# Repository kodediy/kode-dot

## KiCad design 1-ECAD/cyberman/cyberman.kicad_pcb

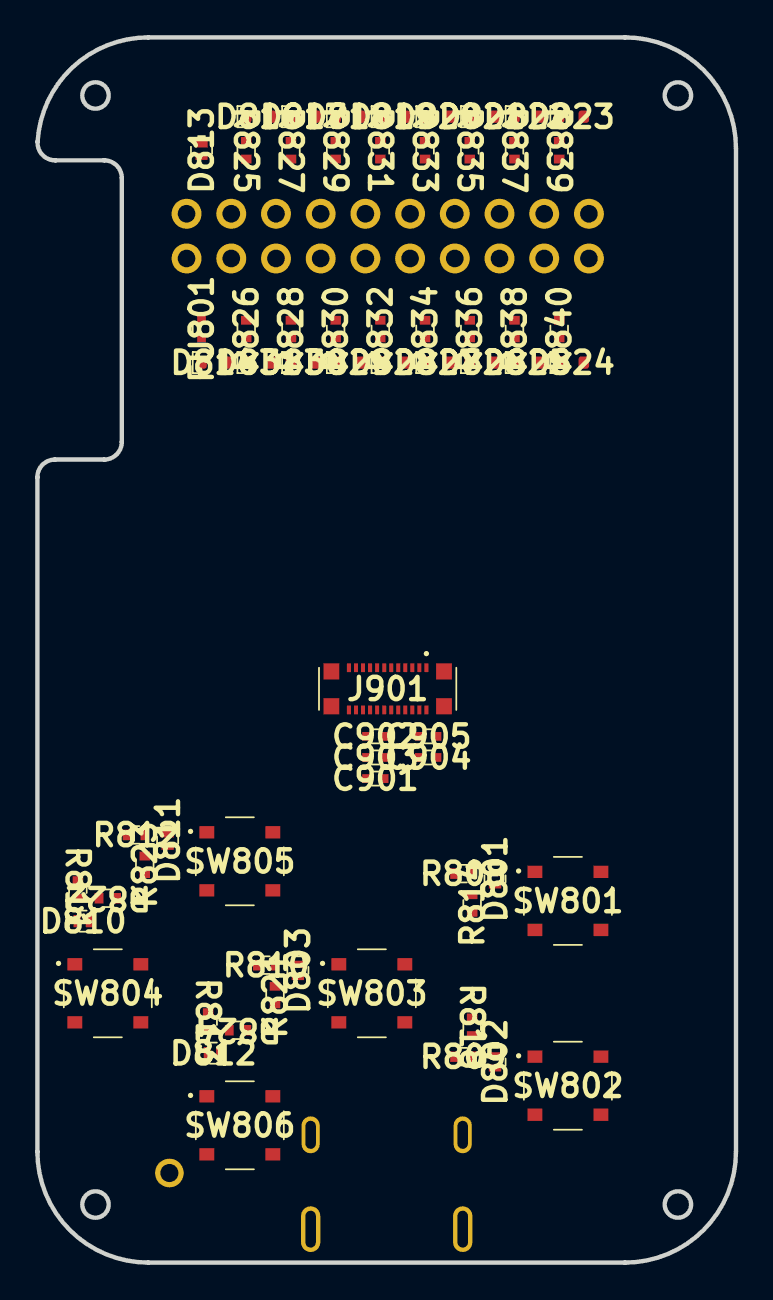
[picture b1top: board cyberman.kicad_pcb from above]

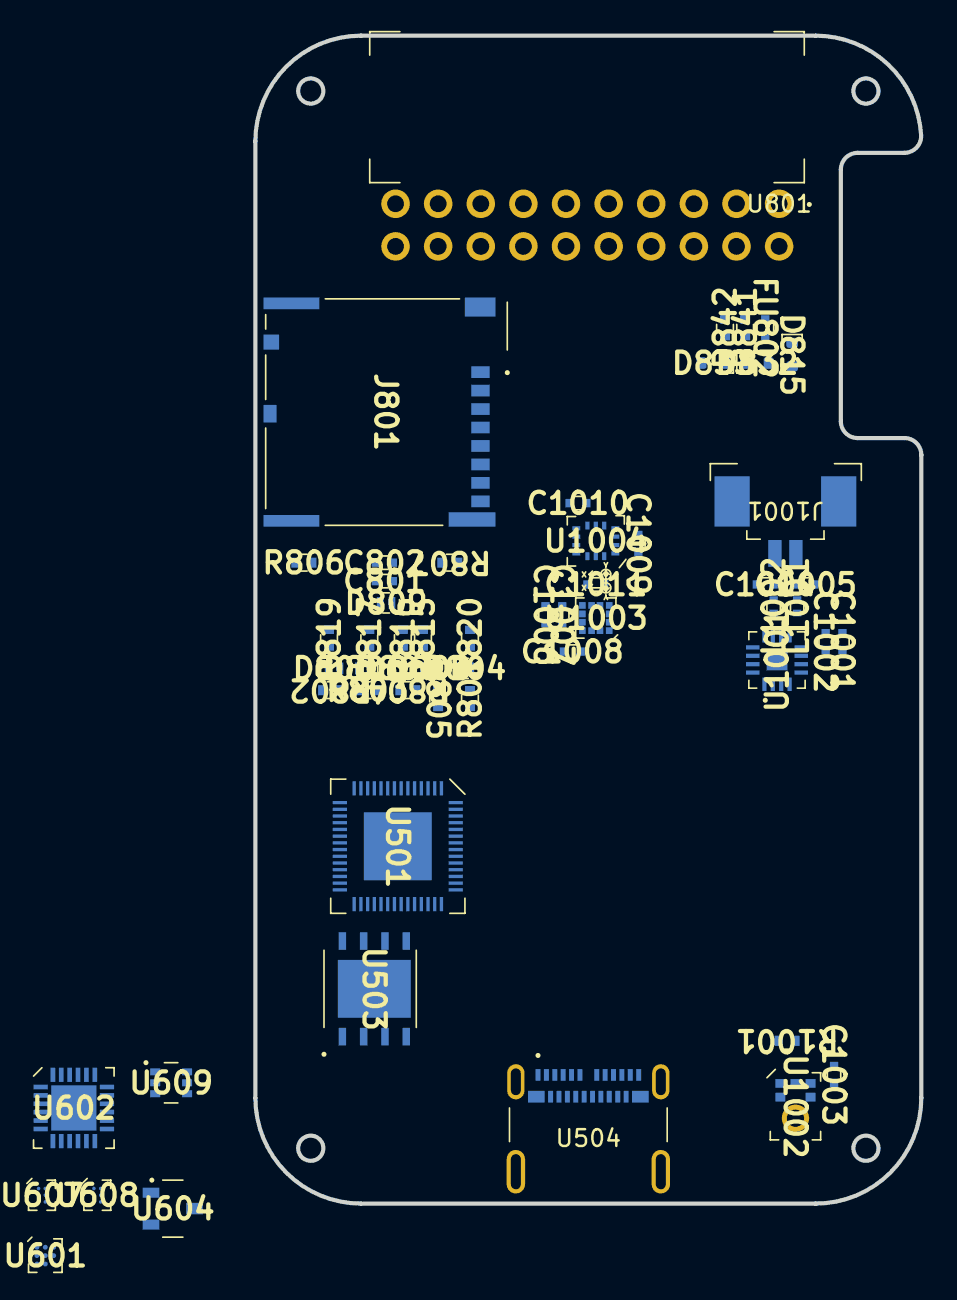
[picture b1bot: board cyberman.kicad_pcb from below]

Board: 4 copper layers, 39.7 x 69.6 mm, 121 parts (56 on the bottom side), 85 nets, no tracks yet.

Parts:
C801, C802, C901, C904, C1001, C1006: CC0402MRX5R6BB106; C_0402
C902, C903, C905, C1002, C1003, C1007, C1008, C1009, C1010: CC0402KRX7R8BB104; C_0402
C1004, C1005: CC0402KRX7R8BB221; C_0402
C1011: CC0402KRX5R8BB224; C_0402
D801, D802, D803, D804, D805, D806, D807, D808, D809, D810, D811, D812, D813: LESD8D3.3CAT5G
D814, D815, D816, D817, D818, D819, D820, D821, D822, D823, D824, D825, D826, D827, D828, D829, D830, D831, D832, D833: LESD5D5.0CT1G
FU801, FU802: ERBRD2R00X; ERBRD0R63X
J801: 5033981892
J901: YXT-BB10-24S-02
J1001: 532610271
L1001, L1002: BLM15PX331SZ1D
R801, R802, R803, R804, R805, R806, R807: RC0402FR-0747KL; R_0402
R808, R809, R810, R811, R812, R813: RC0402FR-0710KL; R_0402
R814, R818, R821, R822, R823, R824: RC0402FR-07330RL; R_0402
R815, R820: RC0402FR-07150RL; R_0402
R816, R817, R819, R825, R826, R827, R828, R829, R830, R831, R832, R833, R834, R835, R836, R837, R838, R839, R840, R841, R842: RC0402FR-0751RL; R_0402
R1001: RC0402FR-07100KL; R_0402
SW801, SW802, SW803, SW804, SW805, SW806: SKRMAAE010
U501: ESP32-S3R16V
U503: W25Q128JWPIQ
U504: 1054500101
U601: BQ27220YZFR
U602: BQ25896RTWR
U604: RS3221-3.3YF3
U607, U608: LM3281YFQR
U609: MMDT2907A-7-F
U801: PM254-2-10-W-8.5
U1001: MAX98357A; MAX98357AETE+T
U1002: ICS-43434
U1003: LIS2MDLTR
U1004: LSM6DSOTR

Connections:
+3V3: C1001.1, C1002.1, C1003.1, C1006.1, C1007.1, C1008.1, C1009.1, C1010.1, R808.1, R809.1, R810.1, R811.1, R812.1, R813.1, U608.A1 (FB), U1001.7 (VDD), U1001.8 (VDD), U1002.5 (VDD), U1003.3 (CS), U1003.9 (VDD), U1003.10 (VDDIO), U1004.1 (SDO/SA0), U1004.5 (VDDIO), U1004.8 (VDD), U1004.12 (CS)
+BATT: U601.C1 (SRP), U601.C3 (BAT)
/Project Architecture/Display/DSP.RST: J901.9 (RST), J901.21 (TP-RST)
/Project Architecture/MCU - IOs/BUTTON.BACK: R818.1, U501.37 (SPICLK_P)
/Project Architecture/MCU - IOs/BUTTON.SELECT: R814.1, U501.36 (SPICLK_N)
/Project Architecture/MCU - IOs/SD.CD: D804.1, R801.2, R820.1
/Project Architecture/MCU - IOs/SD.CLK: D806.1, R803.2, R817.1, U501.23 (GPIO17)
/Project Architecture/MCU - IOs/SD.CS: D808.1, R805.2, R815.1, U501.22 (XTAL_32K_N)
/Project Architecture/MCU - IOs/SD.MISO: D805.1, R802.2, R819.1, U501.27 (GPIO21)
/Project Architecture/MCU - IOs/SD.MOSI: D807.1, R804.2, R816.1, U501.24 (GPIO18)
/Project Architecture/MCU - IOs/SPICLK: U501.33 (SPICLK), U503.6 (CLK)
/Project Architecture/MCU - IOs/SPICS0: U501.32 (SPICS0), U503.1 (~CS)
/Project Architecture/MCU - IOs/SPID: U501.35 (SPID), U503.5 (DI(IO0))
/Project Architecture/MCU - IOs/SPIHD: U501.30 (SPIHD), U503.7 (IO3)
/Project Architecture/MCU - IOs/SPIQ: U501.34 (SPIQ), U503.2 (DO(IO1))
/Project Architecture/MCU - IOs/SPIWP: U501.31 (SPIWP), U503.3 (IO2)
/Project Architecture/Peripherals/1: D816.1, R825.1
/Project Architecture/Peripherals/2: D817.1, R827.1
/Project Architecture/Peripherals/3: D818.1, R829.1
/Project Architecture/Peripherals/4: D819.1, R831.1
/Project Architecture/Peripherals/5: D820.1, R833.1
/Project Architecture/Peripherals/6: D821.1, R835.1
/Project Architecture/Peripherals/7: D822.1, R837.1
/Project Architecture/Peripherals/8: D823.1, R839.1
/Project Architecture/Peripherals/9: D831.1, R826.1
/Project Architecture/Peripherals/10: D830.1, R828.1
/Project Architecture/Peripherals/11: D829.1, R830.1
/Project Architecture/Peripherals/12: D828.1, R832.1
/Project Architecture/Peripherals/13: D827.1, R834.1
/Project Architecture/Peripherals/14: D826.1, R836.1
/Project Architecture/Peripherals/15: D825.1, R838.1
/Project Architecture/Peripherals/16: D824.1, R840.1
/Project Architecture/Peripherals/BOARD_I2C.SCL: D832.1, R841.1
/Project Architecture/Peripherals/BOARD_I2C.SDA: D833.1, R842.1
/Project Architecture/Sensors and Audio/I2C_BOARD.SCL: U1003.1 (SCL/SPC), U1004.13 (SCL)
/Project Architecture/Sensors and Audio/I2C_BOARD.SDA: U1003.4 (SDA/SDI/SDO), U1004.14 (SDA)
/Project Architecture/Sensors and Audio/I2S.SCK: U1001.16 (BCLK), U1002.4 (SCK)
/Project Architecture/Sensors and Audio/I2S.SD: R1001.1, U1001.1 (DIN), U1002.6 (SD)
/Project Architecture/Sensors and Audio/I2S.WS: U1001.14 (LRCLK), U1002.1 (WS)
EXT_3V3: C801.1, C802.1, C901.1, C902.1, C903.1, C904.1, C905.1, D809.1, D813.2, J801.4 (VDD), J901.15 (VCC), J901.16 (VCI_EN), J901.17 (VBAT), J901.23 (TP-VDD), R801.1, R802.1, R803.1, R804.1, R805.1, R806.1, R807.1, U607.A1 (FB), U801.1
GND: C801.2, C802.2, C901.2, C902.2, C903.2, C904.2, C905.2, C1001.2, C1002.2, C1003.2, C1004.2, C1005.2, C1006.2, C1007.2, C1008.2, C1009.2, C1010.2, C1011.2, D801.2, D802.2, D803.2, D804.2, D805.2, D806.2, D807.2, D808.2, D809.2, D810.2, D811.2, D812.2, D813.1, D814.2, D815.2, D816.2, D817.2, D818.2, D819.2, D820.2, D821.2, D822.2, D823.2, D824.2, D825.2, D826.2, D827.2, D828.2, D829.2, D830.2, D831.2, D832.2, D833.2, J801.6 (VSS), J801.9 (VSS), J901.13 (GND), J901.18 (GND), J901.24 (GND), J901.P1 (SHELL), J901.P2 (SHELL), J901.P3 (SHELL), J901.P4 (SHELL), R1001.2, SW801.2, SW802.2, SW803.2, SW804.2, SW805.2, SW806.2, U503.4 (GND), U504.A1 (GND), U504.A12 (GND), U504.B1 (GND), U504.B12 (GND), U601.B2 (VSS), U602.9 (~CE), U602.17 (PGND), U602.18 (PGND), U604.1 (GND), U801.19, U801.20, U1001.3 (GND), U1001.11 (GND), U1001.15 (GND), U1001.17 (EP), U1002.2 (LR), U1002.3 (GND), U1003.6 (GND), U1003.8 (GND), U1004.2 (SDx), U1004.3 (SCx), U1004.6 (GND), U1004.7 (GND)
GNDPWR_EXT: U607.C2 (GND), U608.C2 (GND)
unnamed: U504.A6 (D+), U504.B6 (D+)
unnamed: U504.A7 (D-), U504.B7 (D-)
unnamed: U602.19 (SW), U602.20 (SW)
unnamed: D801.1, R808.2, R814.2, SW801.1
unnamed: D802.1, R809.2, R818.2, SW802.1
unnamed: D803.1, R810.2, R821.2, SW803.1
unnamed: D810.1, R811.2, R822.2, SW804.1
unnamed: D811.1, R812.2, R823.2, SW805.1
unnamed: D812.1, R813.2, R824.2, SW806.1
unnamed: FU801.2, U801.2
unnamed: J801.2 (CD/DAT3), R815.2
unnamed: J801.5 (CLK), R817.2
unnamed: J801.3 (CMD), R816.2
unnamed: J801.7 (DAT0), R819.2
unnamed: J801.8 (DAT1), R806.2
unnamed: J801.1 (DAT2), R807.2
unnamed: J801.10 (SW_DTCT), R820.2
unnamed: C1005.1, J1001.1, L1001.2
unnamed: C1004.1, J1001.2, L1002.2
unnamed: U609.2, U609.3, U609.5
unnamed: R825.2, U801.3
unnamed: R826.2, U801.4
unnamed: R827.2, U801.5
unnamed: R828.2, U801.6
unnamed: R829.2, U801.7
unnamed: R830.2, U801.8
unnamed: R831.2, U801.9
unnamed: R832.2, U801.10
unnamed: R833.2, U801.11
unnamed: R834.2, U801.12
unnamed: R835.2, U801.13
unnamed: R836.2, U801.14
unnamed: R837.2, U801.15
unnamed: R838.2, U801.16
unnamed: R839.2, U801.17
unnamed: R840.2, U801.18
unnamed: U601.C2 (SRN), U602.13 (BAT), U602.14 (BAT)
unnamed: L1002.1, U1001.10 (OUTN)
unnamed: L1001.1, U1001.9 (OUTP)
unnamed: C1011.1, U1003.5 (C1)
SYS: U602.15 (SYS), U602.16 (SYS), U607.A2 (VIN), U607.B1 (MODE), U608.A2 (VIN), U608.B1 (MODE), U608.C1 (EN)
VBUS: D814.1, D815.1, FU801.1, FU802.1, U602.1 (VBUS), U609.1
VUSB_5V: U504.A4 (VBUS), U504.A9 (VBUS), U504.B4 (VBUS), U504.B9 (VBUS), U609.4

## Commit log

2024-10-30 add things
2024-10-30 add gitkeep
2024-10-30 Create project
2024-10-30 Version demo inicial de la web para el sistema operativo. Codigo ejemplo de arduino. Carpeta ConfiguracionesBoard con las configuraciones para cargar desde mac usando arduino
2024-10-31 add esp32 library
2024-11-02 Eliminados archivos .DS_Store del índice de Git
2024-11-02 Añadido .DS_Store al .gitignore
2024-11-02 Carpeta para archivos mecanicos
2024-11-04 esp32 supply
2024-11-05 update power sche
2024-11-12 power
2024-11-19 esp32
2024-11-19 esp32 hard guidelines
2024-11-19 microSD and LCD connector
2024-11-22 add sensor page
2024-11-22 add mic and speaker
2024-11-23 add bus and display connection
2024-11-29 connections
2024-12-02 esp and usbc footprints
2024-12-03 add expander io and pic
2024-12-05 add new footprints
2024-12-09 footpritn day
2024-12-10 sensor page closed
2024-12-10 add buttons
2024-12-11 new changes
    close display page and peripheral schematic
2024-12-14 add fuse and place external connector
2024-12-16 change layout
2024-12-17 edit power page
2024-12-17 power page almost done
2024-12-18 new footprints
2024-12-18 power page close
    siuuuuuuuuuuuu
